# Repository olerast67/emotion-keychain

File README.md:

English | [Русский](README.ru.md)

<div align="center">

# Emotion keychain

**A backpack keychain with a small white OLED screen and a character living on it.**<br>
It blinks, looks around, laughs, gets angry, falls asleep in the dark and reacts to taps, shaking, sound and light.

[Owner's guide](docs/user-guide.en.md) · [Engine](docs/engine.en.md) · [Emotions](docs/emotions.en.md) · [Voice](docs/sound.en.md) · [Encounters](docs/encounters.en.md) · [Hardware](docs/hardware.en.md) · [Board](hardware/rev-b/README.en.md) · [Case](hardware/rev-b/case/README.en.md) · [Power](docs/power.en.md) · [Plan](docs/plan.en.md)

</div>

---

> [!IMPORTANT]
> **Project status**
> - **Works today:** the face engine, the simulators (desktop and browser) and the **ESP32 test stand** — a cheap dev board with a real OLED screen.
> - **Designed, not built yet:** the **rev B keychain board**. It passes DRC and a full simulation of its firmware, but it has **not been fabricated or tested** on real hardware. Order it only if you are fine with being the first to try it.
> - **Battery life numbers are estimates** from a simulation of the board, not measurements.

## Three ways in

| | | |
|---|---|---|
| **Try it in the browser** | No hardware, nothing to install. Tap the face, shake it, turn off the lights, start a duel with a neighbour. | [olerast67.github.io/emotion-keychain](https://olerast67.github.io/emotion-keychain/) |
| **Build the ~$10 ESP32 version** | Any ESP32 dev board (C5, classic, C3 or S3), a 0.96″ SSD1306 module and four wires. Optional touch button and piezo. Flash it from the browser on [olerast.com](https://olerast.com/projects/emotion-keychain/flash). | [ESP32 stand](firmware/README.en.md#esp32-stand) |
| **Make the rev B keychain** | The real thing: a 30 × 46 mm nRF52840 board in an acrylic case, with sensors, a piezo voice, vibration and a Li-Po cell. Not yet tested — see the status above. | [Board](hardware/rev-b/README.en.md) · [Case](hardware/rev-b/case/README.en.md) · [Firmware](firmware/README.en.md#rev-b-board) |

## Features

- **139 emotions.** Joy, laughter, sadness, anger, surprise, sleep, dizziness, "listening", "eating" while charging — and memes: the screaming soyjak, Lenny, `¯\_(ツ)_/¯`, FFFUUU, `$_$`, the table flip. [Full catalogue](docs/emotions.en.md).
- **Every face is alive.** Blinking, gaze, moving pupils and a signature gesture each: breathing, eyebrows, squinting, head tilt, chatter. Transitions are smooth, and eye shape changes hide behind a blink.
- **Ten characters:** playful, grumpy, sleepy, shy, curious, chill, drama, glitchy, sly and kind. Each has its own resting face, its own answer to touches, its own hobbies, tempo and voice. The character and looks come from the chip's serial number, so no two keychains are the same. One in a hundred is legendary, with a golden cyber eye.
- **It reacts to the world.** Taps, shaking, falls, claps, music, darkness, cold, charging, long loneliness. Reactions rotate, and annoyance has a ladder from "-_-" to flipping the table.
- **Growth and achievements.** It starts with 44 emotions and unlocks the rest as "implants" for days together, touches, steps and encounters — about a month in all. On top: a streak of days together and 24 achievements with a trophy, from FIRST FRIEND to MARATHON and 1337.
- **Synthesized voice.** A piezo buzzer answers touches with short "words" made of notes, R2-D2 style, and every character has its own pitch and manner. Scenes have their own music, from a modem handshake during a "hack" to Happy Birthday. [How it sounds](docs/sound.en.md).
- **Encounters and duels over Bluetooth, without pairing.** Two keychains nearby find each other on their own, become friends day by day from NEW FRIEND to BFF, duel, and the older one gifts the younger an emotion. After a duel they chat in a beeping cipher. [Protocol](docs/encounters.en.md).
- **Surprises and easter eggs.** Fake hacks, hiding, reboots, ERROR 404: MOOD NOT FOUND, a ":(" blue screen, holidays and your birthday, H4X0R MODE at 13:37, and a logo bouncing until it hits the corner while charging.
- **Three themes:** classic, cyberpunk and retro (big pixels like an old handheld).
- **Kind to the battery.** A frame is drawn only when the face changes, only the changed parts go to the screen, and the CPU sleeps between frames.
- **One codebase everywhere:** the rev B firmware (nRF52840), the ESP32 stand, desktop simulators and the browser page.

<div align="center">

</div>

## How it works

```mermaid
flowchart LR
  IMU["Accelerometer<br/>tap · shake · fall · steps"] --> B
  MIC["Microphone<br/>speech · music · clap"] --> B
  LUX["Light sensor<br/>dark · bright"] --> B
  PWR["Battery and USB<br/>charge · charging"] --> B
  CLK["Clock<br/>day · night"] --> B
  B["Behavior<br/>mood and reactions"] --> E["FaceEngine<br/>face · transitions · gestures"]
  E -- "changed windows only" --> D["SSD1306<br/>128×64 over I2C"]
  B --> V["Voice<br/>phrases · scene music"]
  V -- "PWM frequency" --> Z["Piezo"]
```

Details are in the [engine description](docs/engine.en.md).

## The rev B keychain

<div align="center">

</div>

<table>
<tr>
<td width="50%"></td>
<td width="50%"></td>
</tr>
<tr>
<td align="center">Assembled: the screen behind a clear cover</td>
<td align="center">Exploded: acrylic layers, screen module and board</td>
</tr>
</table>

| | |
|---|---|
| **Screen** | white 0.96″ OLED, SSD1306, 128×64 |
| **Brain** | nRF52840: Raytac MDBT50Q module on the rev B board |
| **Sensors** | LIS3DH accelerometer, PDM microphone, LTR-303ALS light sensor, button |
| **Voice and feedback** | piezo buzzer, vibration motor |
| **Power** | protected Li-Po cell, 402025, 502025 or 602025 (150–250 mAh); USB-C charging at 100 mA, only at 10–42 °C by the nRF die temperature |
| **Board** | 30 × 46 mm plus a ring tab, 4 layers, production files for JLCPCB and PCBWay |
| **Case** | laser-cut acrylic "sandwich", 35 × 51 mm, 18.8 / 19.8 / 20.8 mm thick in three versions S, M, L for different cells |
| **Battery life (estimate)** | a typical day — about 11, 15 and 18 days (S, M, L); 16 h of face a day — about 3–5 days. **Simulation estimate, not measured** |

- **Generated from one description.** Schematic, placement, routing, Gerber, BOM and CPL are built by scripts from [`netlist.py`](hardware/rev-b/gen/netlist.py); nothing is edited by hand in KiCad.
- **Four layers,** a solid ground plane, the antenna at the edge with no copper under it.
- **Assembly:** the factory places the small parts on both sides; by hand you add the screen module, the cell and the vibration motor (about 15 minutes).
- **Ready to order:** production files are in [`hardware/rev-b/out`](hardware/rev-b/out) and [`hardware/rev-b/out/panel`](hardware/rev-b/out/panel). Remember that nobody has built one yet.

Parts, stack-up and sourcing: [docs/hardware.en.md](docs/hardware.en.md). Current budget: [docs/power.en.md](docs/power.en.md). Using the keychain: [owner's guide](docs/user-guide.en.md).

## Repository layout

```
engine/          face engine: C++20, no heap, no exceptions, no libm
  include/face/  headers: face parameters, catalogue, engine, behaviour
  src/           rendering, animation, 139 emotion presets, behaviour
  tests/         tests with no external dependencies
firmware/        firmware: rev B board (nRF52840) and the ESP32 stand
  src/keychain/  rev B: sensors, radio, power, console
  bootloader/    bootloader for the first flash over SWD
  release/       ready-made firmware files
hardware/
  rev-b/         the rev B board: KiCad, Gerber, BOM, CPL, schematic PDF
    gen/         generators: netlist.py, placement, routing, production files
    case/        acrylic case: cut files and a 3D viewer
sim/
  cli/           facegen — GIFs, contact sheets, benchmark, catalogue
  sdl/           facesim — desktop window simulator
  web/           browser simulator (the engine in WebAssembly)
docs/            engine, emotions, hardware, power, plan, owner's guide
tools/           helper scripts
LICENSES/        licence texts (see REUSE.toml)
```

## Build

You need CMake 3.16+ and a C++20 compiler (GCC 10+ or Clang 12+). SDL2 is only needed for the window simulator.

```sh
cmake -S . -B build -DCMAKE_BUILD_TYPE=Release
cmake --build build

./build/face_tests                              # engine tests
./build/facegen list                            # all emotions and clips
./build/facegen anim lenny out/lenny.gif        # one emotion as a GIF
./build/facegen trans neutral laugh out/t.gif   # a transition between two emotions
./build/facegen sheet out/all.gif --scale 2     # contact sheet of all emotions
./build/facegen scene hack out/hack.gif         # a surprise scene (--theme cyber for cyberpunk)
./build/facegen sound all out/voice.wav         # the keychain's voice as WAV (--serial N for another one)
./build/facesim                                 # window with a face (if SDL2 is present)
```

Browser simulator (needs clang with the wasm32 target and wasm-ld from lld):

```sh
sim/web/build.sh    # then open sim/web/dist/index.html, no server needed
```

Firmware (PlatformIO):

```sh
cd firmware
pio run -e esp32c5 -t upload && pio device monitor   # ESP32 stand (also esp32dev, esp32c3, esp32s3)
pio run -e keychain                                  # rev B board → .pio/build/keychain/
```

Ready-made firmware files are in [`firmware/release/`](firmware/release/README.en.md). The first flash of a rev B board goes over SWD with a Raspberry Pi Pico as the programmer, see the [bootloader notes](firmware/bootloader/README.en.md). Board and case generators (KiCad 7, Python) are described in the [board README](hardware/rev-b/README.en.md) and [hardware overview](hardware/README.en.md).

## How this was made

This project was built by a non-expert — not an electronics engineer or a professional programmer — working with an AI assistant, Claude by Anthropic. The engine, the firmware, the board generators, the case and these docs were written in conversation, then checked with tests, simulation, DRC and many review passes. That is also why the status box above is so careful: what has not been tested on real hardware is clearly marked. Bug reports and fixes from people who know better are very welcome.

## Licences

The project is fully open source. You may build, modify and sell keychains, boards and cases under these terms:

| What | Licence | File |
|---|---|---|
| Code: `engine/`, `firmware/`, `sim/`, `tools/`, CMake and scripts | Apache-2.0 | [LICENSE](LICENSE), [NOTICE](NOTICE) |
| Hardware: `hardware/` — KiCad files, generators, Gerber, BOM/CPL, case files | CERN-OHL-W-2.0 | [hardware/LICENSE](hardware/LICENSE), [text](LICENSES/CERN-OHL-W-2.0.txt) |
| Documentation and images: `docs/`, README files, `*.md`, PNG and GIF | CC-BY-4.0 | [text](LICENSES/CC-BY-4.0.txt) |

[REUSE.toml](REUSE.toml) maps every path to its licence. Firmware binaries also contain third-party code under its own licences (the Adafruit nRF52 Arduino core under LGPL-2.1, the Nordic SoftDevice S140 under Nordic's licence, and more): see [THIRD_PARTY_NOTICES.md](THIRD_PARTY_NOTICES.md).

**Trademarks.** The project name, logo, mascot and character art style and the OLERAST brand are not licensed. Forks and derivative products must use a different name; "compatible with Emotion keychain" or "based on Emotion keychain" is fine. See [TRADEMARKS.md](TRADEMARKS.md).

## Contributing

Ideas for new emotions are easiest to file with the [issue template](https://github.com/olerast67/emotion-keychain/issues/new/choose). To add an emotion yourself: add its id to `FACE_EXPR_LIST` in [`engine/include/face/expressions.h`](engine/include/face/expressions.h), describe the preset in [`engine/src/expressions.cpp`](engine/src/expressions.cpp), check it with `./build/facegen anim <id> out/x.gif` and `./build/face_tests`, and regenerate the catalogue with `./build/facegen catalog docs/emotions.md` (CI checks that it matches the code).

## Support

The project is free and open: no ads, no paid features, no accounts. Donations go into test boards, parts and the time it takes to get rev B from "designed" to "tested on real hardware".

&nbsp;

A star on the repository, a photo of the stand you built, or a bug report helps too.

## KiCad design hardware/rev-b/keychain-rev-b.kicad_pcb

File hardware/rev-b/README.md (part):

[English](README.en.md) | Русский

# Плата rev B

> **Статус:** готова к заказу. Перед выпуском плату исправили по полному предрелизному аудиту и независимой проверке: SA0 акселерометра на VDD, ёмкость на выходе REG0 в норме Nordic, перемычки экрана дальше от штырей, заряд по разрешению прошивки, уровень статуса заряда, TVS на VBUS, панель для монтажа, нормы JLCPCB по отверстиям и шёлку ([список](#проверка-перед-заказом)). Переходные 0.25/0.55 мм, переходных в площадках нет. DRC — 0 ошибок, 0 несоединённых, 0 предупреждений (`out/keychain-rev-b-drc.rpt`). Файлы для заказа уже собраны: одна плата — в `out/`, [панель для монтажа](#панель-для-монтажа) — в `out/panel/`. Перед заказом пройдите список [«Что сверить»](#что-сверить-перед-заказом).

Своя плата брелока: модуль nRF52840 (Raytac MDBT50Q), зарядка Li-Po от USB-C, датчики, пищалка, вибро и кнопка. Модуль экрана SSD1306 0.96″ стоит над ней на ушках акриловых рамок корпуса, ячейка — между ними. Как устроена схема и почему так — в [описании железа](../../docs/hardware.md).

Корпус из акрила под лазерную резку и 3D-просмотр собранного брелока — в [`case/`](case/README.md).

Всё генерируется скриптами из одного описания `gen/netlist.py`: схема, плата, трассировка, Gerber, BOM и CPL. Руками в KiCad ничего не правится.

**Для заказа ничего запускать не нужно.** Плата `keychain-rev-b.kicad_pcb` разведена и проверена, файлы для заводов лежат в `out/` и `out/panel/` — их загружают как есть ([JLCPCB](#заказ-на-jlcpcb), [PCBWay](#заказ-на-pcbway)). Скрипты нужны, только чтобы изменить плату:

```sh
cd hardware/rev-b/gen
python3 build.py place --force  # расставить детали заново — плата БЕЗ дорожек (out/work/place-*.png)
python3 build.py route     # переходные земли и питания, шины питания, Freerouting, доводка, заливки, DRC
python3 build.py finish    # доводка разведённой платы без перетрассировки — только проверка, без записи
python3 build.py finish --force  # то же с записью: паста, шёлк и надписи из netlist.py, отверстия
python3 build.py fab       # DRC, Gerber, BOM, CPL, файлы PCBWay, чертежи, превью, панель → out/, out/panel/ (нужен KiKit, ниже)
python3 build.py panel     # DRC платы, потом только панель → out/panel/ (нужен KiKit, ниже)
python3 schematic.py       # схема A3 + сверка с netlist.py → out/keychain-rev-b-schematic.pdf
```

- **`place` и `route` заменяют разведённую плату:** `place` — платой без дорожек, `route` — новой разводкой (Freerouting от прогона к прогону разводит по-разному). Поэтому без `--force` оба отказываются, если в плате уже есть дорожки. После `place --force` нужен `route` — уже без `--force`, дорожек ведь нет.
- **`route` и `finish --force` записывают плату только после чистого DRC.** Не прошла — `keychain-rev-b.kicad_pcb` не тронута, а результат для разбора лежит в `out/work/keychain-rev-b-*-failed.kicad_pcb`, отчёт — в `out/work/keychain-rev-b-drc.rpt`. `route` сначала проверяет Java и Freerouting и только потом трогает плату. `finish` без `--force` ничего не пишет: доводит плату в памяти, гоняет DRC и говорит, изменилась бы плата.
- **`fab` сам прогоняет DRC.** Если есть ошибки, несоединённые площадки, в плате нет дорожек или на площадках деталей, которые завод не ставит, есть паста, он ничего не пишет ни в `out/`, ни в `out/panel/`. Панель он собирает раньше файлов одной платы, в черновик `out/work/panel-new`: не собралась или не прошла проверки — `out/` и `out/panel/` не тронуты; собралась — пишутся файлы одной платы, и черновик целиком заменяет `out/panel/`. `build.py panel` сначала так же проверяет плату и только потом собирает панель.
- **Отчёт `out/keychain-rev-b-drc.rpt` пишет только `fab`** и только для платы, которая прошла. Отчёты `route` и `finish` — в `out/work/`.
- **Если что-то пошло не так**, вернуть плату и файлы из репозитория:

  ```sh
  git checkout -- hardware/rev-b/keychain-rev-b.kicad_pcb hardware/rev-b/Keychain.pretty hardware/rev-b/out
  ```

Нужен именно KiCad 7 (`pcbnew` для Python и `kicad-cli`): на KiCad 8 и новее скрипты не работают. Для превью и чертежей — `cairosvg` (`pip install cairosvg`, путь можно дать в `CAIROSVG`) или `rsvg-convert`, и Pillow. Для `route` — Java 21 и [Freerouting](https://github.com/freerouting/freerouting) 2.1, путь к jar — в `FREEROUTING_JAR`. Для панели — [KiKit](https://github.com/yaqwsx/KiKit) 1.5.1 в Python, где виден `pcbnew` KiCad 7:

```sh
python3 -m venv --system-site-packages ~/kikit-venv && ~/kikit-venv/bin/pip install kikit==1.5.1
KIKIT_PYTHON=~/kikit-venv/bin/python python3 build.py fab     # и так же build.py panel
```

`fab` и `panel` берут KiKit из того `python3`, которым запущены, а если там его нет — из Python по пути в `KIKIT_PYTHON`. Без KiKit `fab` останавливается до того, как что-то записать. `build.py fab --no-panel` собирает файлы одной платы и удаляет `out/panel/`: старая панель уже не совпадала бы с платой.

## Стек и размеры

- **Плата:** 30 × 46 мм и ушко для кольца по центру сверху (полукруг R4.5, отверстие 3.2 мм без металлизации), 4 слоя, 1.6 мм, углы R2.
- **Верхние 18 мм** — модуль nRF антенной к правому краю и датчик света, который смотрит вперёд. Ниже — модуль экрана.
- **Сбоку стек:** стекло и плата модуля экрана → две рамки ячейки из акрила, на их ушках лежит модуль, внутри ячейка Li-Po на тонком двустороннем скотче → эта плата → детали на обороте. Покупных стоек нет.
- **Три версии, S, M и L:** ячейки 402025, 502025 и 602025 (~150, ~200 и ~250 мА·ч), под модулем экрана 6, 7 и 8 мм (рамки ячейки 3 + 3, 3 + 4 и 3 + 5 мм). Плата и прошивка у всех одни и те же, винты корпуса у всех M2 × 25. Ячейка подходит, если:

  > толщина ячейки + 0.3 мм (каптон и скотч под ней) + 0.1 мм (каптон на обороте модуля) + 0.3 мм (вздутие) ≤ высота под модулем − самая высокая деталь на обороте модуля

  Толщину ячейки меряют штангенциркулем в самом толстом месте. Высота под модулем — это две рамки ячейки стопкой, тоже по штангенциркулю: листы акрила гуляют на ±0.1–0.3 мм. Пересчёт по вашим листам — `python3 case.py --sheet 3=… --sheet 4=…` в папке `case/`. Деталь на обороте модуля — 1.1–1.45 мм, смерьте свой модуль. Не влезает — версия на ступень выше. Подробно, вместе с гребёнкой экрана и винтами, — в [README корпуса](case/README.md#три-версии-s-m-l).

| Слой | Что на нём |
|---|---|
| L1 (лицевая) | модуль nRF, датчик света, конденсаторы модуля, площадки ячейки и штырей экрана; длинные сигналы под ячейкой |
| L2 | сплошная земля, без разрезов |
| L3 | шины питания: VBUS, VBAT и VSYS по 0.4 мм, VDD 0.3 мм; медленные сигналы; всё остальное место — земля |
| L4 (оборотная) | остальные детали и сигналы |

Ширины по классам цепей (`NETCLASSES`):

| Класс | Цепи | Дорожка | Где |
|---|---|---|---|
| Power | VBUS, VBAT, VSYS | 0.4 мм | L3 |
| Rail | VDD (3.3 В) | 0.3 мм | L3 |
| Supply | питание экрана и мотора | 0.3 мм | L1, L3, L4 |
| USB | D+, D− | 0.18 мм | L1, L4 |
| Default | сигналы, питание микрофона | 0.15 мм | L1, L3, L4 |

Токи здесь до 0.25 А, 0.4 мм во внутреннем слое держит около 0.7 А. Сигналы в L3 опираются на сплошную землю L2 рядом. Переходные — 0.25/0.55 мм (поясок 0.15 мм): это норма и JLCPCB, и PCBWay.

Порядок трассировки:

1. Каждая площадка земли получает своё переходное в L2, каждая площадка питания — в L3, с зазорами классов цепей.
2. Шины питания в L3 прокладывает свой трассировщик (`gen/powerroute.py`).
3. Сигналы разводит Freerouting; земля для него — плоскость L2, уже проложенное питание закреплено.
4. Что Freerouting не довёл, прокладывает `gen/fixroute.py` по L1, L3 и L4 с переходными, но не в площадках деталей; обрезки и висящие переходные убираются.
5. Заливки земли, сшивка островков, DRC.

Поэтому у питания и земли нет длинных тонких путей по внешним слоям.

## Расстановка по блокам

- **Ушко, лицевая сторона:**
  - модуль;
  - датчик света, его выводы SDA, INT и SCL напротив своих ножек модуля;
  - конденсаторы у ножек питания модуля.
- **Ушко, оборот:**
  - пищалка за модулем, левее антенны;
  - подтяжки шины датчиков;
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
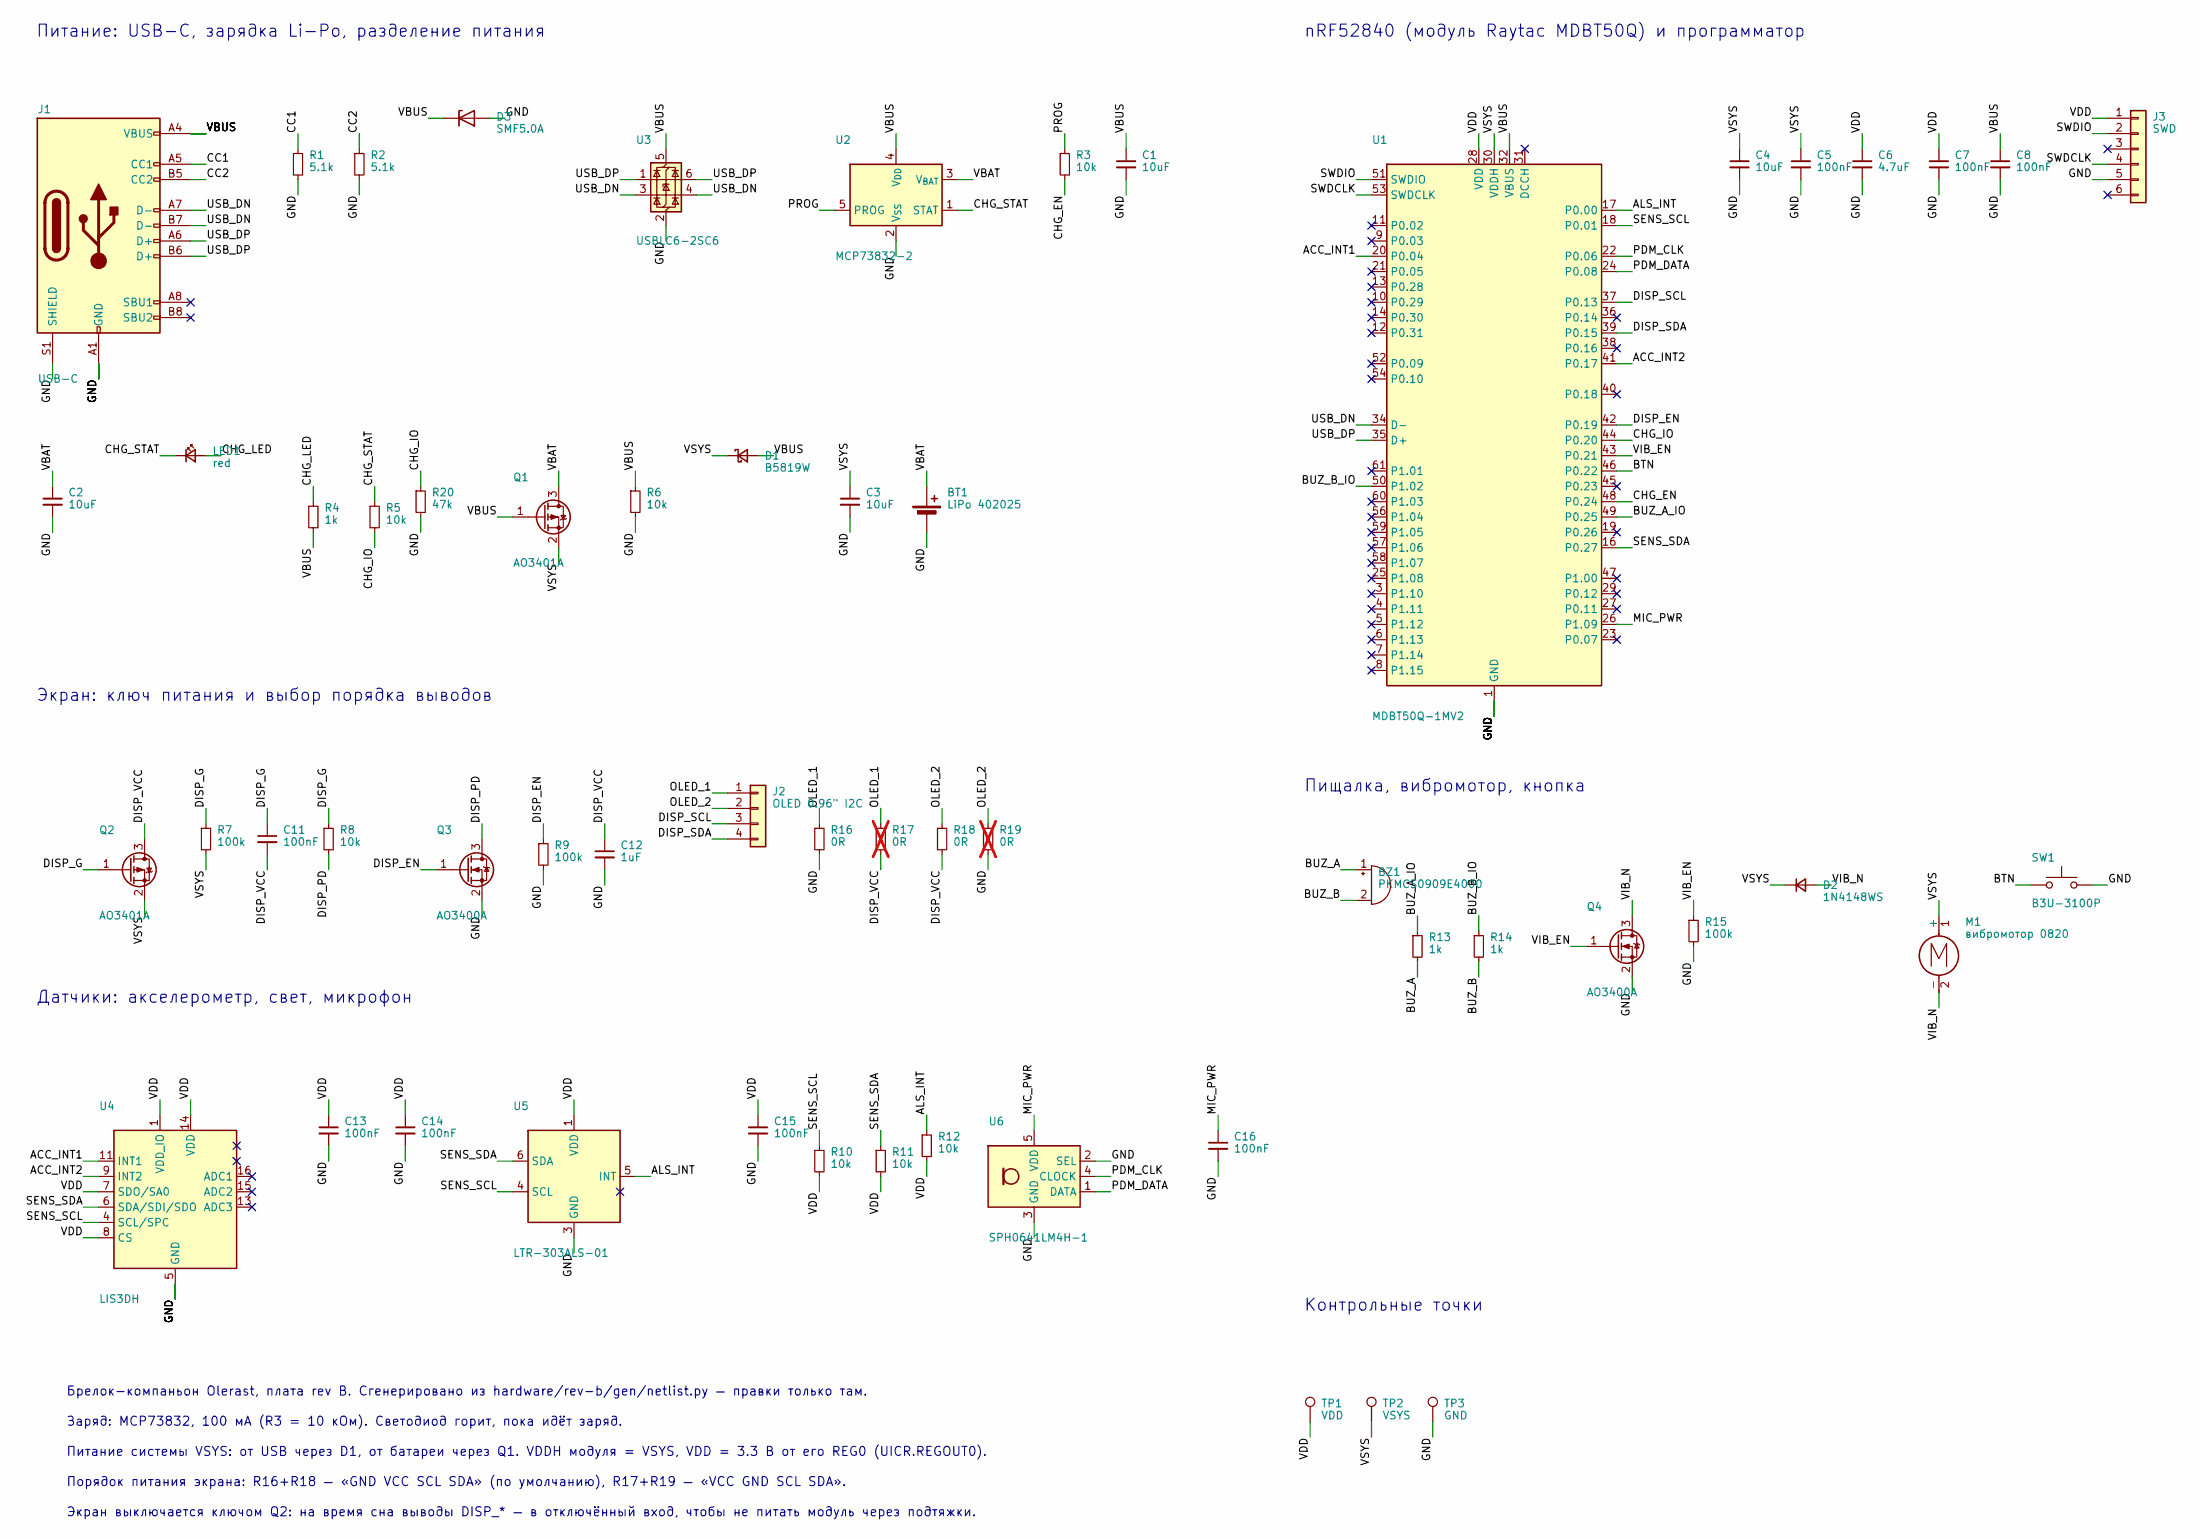
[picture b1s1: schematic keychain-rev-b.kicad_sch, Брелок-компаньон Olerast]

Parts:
BT1: LiPo 402025; LiPo_Pads_20x25mm
BZ1: PKMCS0909E4000; Buzzer_Murata_PKMCS0909E; MPN PKMCS0909E4000-R1; LCSC C910763
C1, C2, C3, C4: 10uF; C_0603_1608Metric; MPN CL10A106KP8NNNC; LCSC C19702
C5, C7, C8, C11, C13, C14, C15, C16: 100nF; C_0402_1005Metric; MPN CL05B104KO5NNNC; LCSC C1525
C6: 4.7uF; C_0603_1608Metric; MPN CL10A475KO8NNNC; LCSC C19666
C12: 1uF; C_0402_1005Metric; MPN CL05A105KA5NQNC; LCSC C52923
D1: B5819W; D_SOD-123; MPN B5819W SL; LCSC C8598
D2: 1N4148WS; D_SOD-323; MPN 1N4148WS; LCSC C2128
D3: SMF5.0A; D_SOD-123F; MPN SMF5.0A; LCSC C1509112
J1: USB-C; USB_C_Receptacle_HRO_TYPE-C-31-M-12; MPN TYPE-C-31-M-12; LCSC C165948
J2: OLED 0.96" I2C; OLED_SSD1306_0.96in_I2C_Module
J3: SWD; Tag-Connect_TC2030-IDC-NL_2x03_P1.27mm_Vertical
LED1: red; LED_0603_1608Metric; MPN KT-0603R; LCSC C2286
M1: вибромотор 0820; VibroMotor_Coin_D8mm
Q1, Q2: AO3401A; SOT-23; MPN AO3401A; LCSC C15127
Q3, Q4: AO3400A; SOT-23; MPN AO3400A; LCSC C20917
R1, R2: 5.1k; R_0402_1005Metric; MPN 0402WGF5101TCE; LCSC C25905
R3, R5, R6, R8, R10, R11, R12: 10k; R_0402_1005Metric; MPN 0402WGF1002TCE; LCSC C25744
R4, R13, R14: 1k; R_0402_1005Metric; MPN 0402WGF1001TCE; LCSC C11702
R7, R9, R15: 100k; R_0402_1005Metric; MPN 0402WGF1003TCE; LCSC C25741
R16, R18: 0R; R_0402_1005Metric; MPN 0402WGF0000TCE; LCSC C17168
R17, R19: 0R; R_0402_1005Metric; MPN 0402WGF0000TCE; LCSC C17168; not fitted
R20: 47k; R_0402_1005Metric; MPN 0402WGF4702TCE; LCSC C25792
SW1: B3U-3100P; SW_SPST_B3U-3100P; MPN B3U-3100P
TP1: VDD; TestPoint_Pad_D1.0mm
TP2: VSYS; TestPoint_Pad_D1.0mm
TP3: GND; TestPoint_Pad_D1.0mm
U1: MDBT50Q-1MV2; Raytac_MDBT50Q; MPN MDBT50Q-1MV2
U2: MCP73832-2; SOT-23-5; MPN MCP73832T-2ACI/OT; LCSC C38066
U3: USBLC6-2SC6; SOT-23-6; MPN USBLC6-2SC6; LCSC C7519
U4: LIS3DH; LGA-16_3x3mm_P0.5mm_LayoutBorder3x5y; MPN LIS3DHTR; LCSC C15134
U5: LTR-303ALS-01; Lite-On_LTR-303ALS-01; MPN LTR-303ALS-01; LCSC C364577
U6: SPH0641LM4H-1; Knowles_LGA-5_3.5x2.65mm; MPN SPH0641LM4H-1; LCSC C497724

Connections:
ACC_INT1: U1.20 (P0.04), U4.11 (INT1)
ACC_INT2: U1.41 (P0.17), U4.9 (INT2)
ALS_INT: R12.1, U1.17 (P0.00), U5.5 (INT)
BTN: SW1.1, U1.46 (P0.22)
BUZ_A: BZ1.1 (+), R13.2
BUZ_A_IO: R13.1, U1.49 (P0.25)
BUZ_B: BZ1.2 (-), R14.2
BUZ_B_IO: R14.1, U1.50 (P1.02)
CC1: J1.A5 (CC1), R1.1
CC2: J1.B5 (CC2), R2.1
CHG_EN: R3.2, U1.48 (P0.24)
CHG_IO: R5.2, R20.1, U1.44 (P0.20)
CHG_LED: LED1.2 (A), R4.1
CHG_STAT: LED1.1 (K), R5.1, U2.1 (STAT)
DISP_EN: Q3.1 (G), R9.1, U1.42 (P0.19)
DISP_G: C11.1, Q2.1 (G), R7.1, R8.1
DISP_PD: Q3.3 (D), R8.2
DISP_SCL: J2.3, U1.37 (P0.13)
DISP_SDA: J2.4, U1.39 (P0.15)
DISP_VCC: C11.2, C12.1, Q2.3 (D), R17.2, R18.2
GND: BT1.2 (-), C1.2, C2.2, C3.2, C4.2, C5.2, C6.2, C7.2, C8.2, C12.2, C13.2, C14.2, C15.2, C16.2, D3.2 (A), J1.A1 (GND), J1.A12 (GND), J1.B1 (GND), J1.B12 (GND), J1.S1 (SHIELD), J3.5, Q3.2 (S), Q4.2 (S), R1.2, R2.2, R6.2, R9.2, R15.2, R16.2, R19.2, R20.2, SW1.2, SW1.3, TP3.1, U1.1 (GND), U1.2 (GND), U1.15 (GND), U1.33 (GND), U1.55 (GND), U2.2 (V_{SS}), U3.2 (GND), U4.5 (GND), U4.10 (GND), U4.12 (GND), U5.3 (GND), U6.2 (SEL), U6.3 (GND)
MIC_PWR: C16.1, U1.26 (P1.09), U6.5 (VDD)
OLED_1: J2.1, R16.1, R17.1
OLED_2: J2.2, R18.1, R19.1
PDM_CLK: U1.22 (P0.06), U6.4 (CLOCK)
PDM_DATA: U1.24 (P0.08), U6.1 (DATA)
PROG: R3.1, U2.5 (PROG)
SENS_SCL: R10.1, U1.18 (P0.01), U4.4 (SCL/SPC), U5.4 (SCL)
SENS_SDA: R11.1, U1.16 (P0.27), U4.6 (SDA/SDI/SDO), U5.6 (SDA)
SWDCLK: J3.4, U1.53 (SWDCLK)
SWDIO: J3.2, U1.51 (SWDIO)
USB_DN: J1.A7 (D-), J1.B7 (D-), U1.34 (D-), U3.3 (I/O2), U3.4 (I/O2)
USB_DP: J1.A6 (D+), J1.B6 (D+), U1.35 (D+), U3.1 (I/O1), U3.6 (I/O1)
VBAT: BT1.1 (+), C2.1, Q1.3 (D), U2.3 (V_{BAT})
VBUS: C1.1, C8.1, D1.2 (A), D3.1 (K), J1.A4 (VBUS), J1.A9 (VBUS), J1.B4 (VBUS), J1.B9 (VBUS), Q1.1 (G), R4.2, R6.1, U1.32 (VBUS), U2.4 (V_{DD}), U3.5 (VBUS)
VDD: C6.1, C7.1, C13.1, C14.1, C15.1, J3.1, R10.2, R11.2, R12.2, TP1.1, U1.28 (VDD), U4.1 (VDD_IO), U4.7 (SDO/SA0), U4.8 (CS), U4.14 (VDD), U5.1 (VDD)
VIB_EN: Q4.1 (G), R15.1, U1.43 (P0.21)
VIB_N: D2.2 (A), M1.2 (-), Q4.3 (D)
VSYS: C3.1, C4.1, C5.1, D1.1 (K), D2.1 (K), M1.1 (+), Q1.2 (S), Q2.2 (S), R7.2, TP2.1, U1.30 (VDDH)

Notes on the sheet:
Питание: USB-C, зарядка Li-Po, разделение питания
nRF52840 (модуль Raytac MDBT50Q) и программатор
Экран: ключ питания и выбор порядка выводов
Пищалка, вибромотор, кнопка
Датчики: акселерометр, свет, микрофон
Контрольные точки
Брелок-компаньон Olerast, плата rev B. Сгенерировано из hardware/rev-b/gen/netlist.py — правки только там.
Заряд: MCP73832, 100 мА (R3 = 10 кОм). Светодиод горит, пока идёт заряд.
Питание системы VSYS: от USB через D1, от батареи через Q1. VDDH модуля = VSYS, VDD = 3.3 В от его REG0 (UICR.REGOUT0).
Порядок питания экрана: R16+R18 — «GND VCC SCL SDA» (по умолчанию), R17+R19 — «VCC GND SCL SDA».
Экран выключается ключом Q2: на время сна выводы DISP_* — в отключённый вход, чтобы не питать модуль через подтяжки.

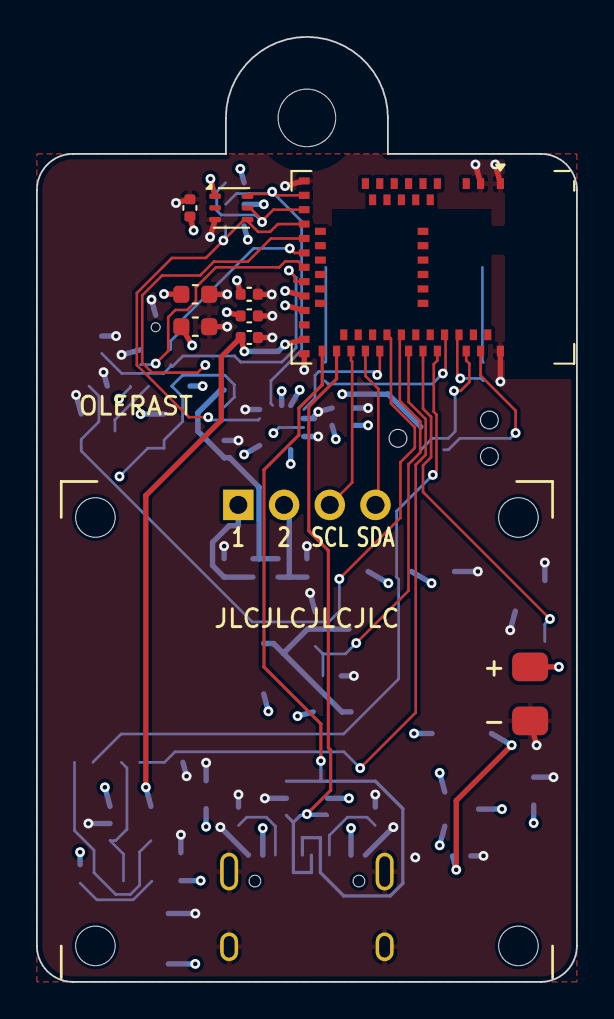
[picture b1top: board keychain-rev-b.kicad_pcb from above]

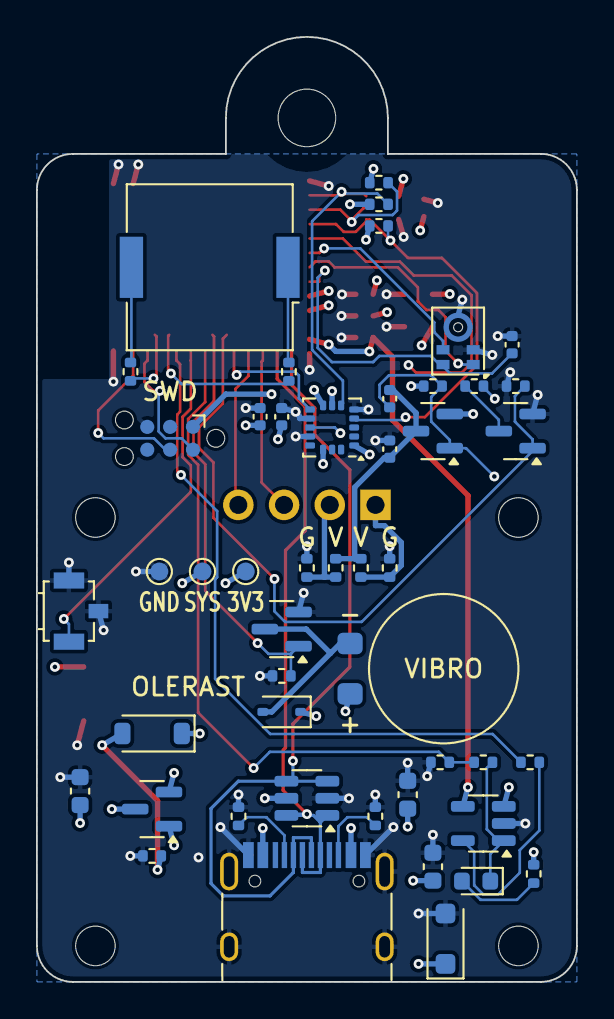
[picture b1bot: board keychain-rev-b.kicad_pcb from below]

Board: 4 copper layers, 30.0 x 52.5 mm, 59 parts (49 on the bottom side), 39 nets.

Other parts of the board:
H1: кольцо брелока или винт корпуса; MountingHole_3.2mm_M3

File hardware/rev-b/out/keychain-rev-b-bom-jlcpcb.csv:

Comment,Designator,Footprint,LCSC,MPN
PKMCS0909E4000,BZ1,Buzzer_Murata_PKMCS0909E,C910763,PKMCS0909E4000-R1
10uF,"C1,C2,C3,C4",C_0603_1608Metric,C19702,CL10A106KP8NNNC
100nF,"C5,C7,C8,C11,C13,C14,C15,C16",C_0402_1005Metric,C1525,CL05B104KO5NNNC
4.7uF,C6,C_0603_1608Metric,C19666,CL10A475KO8NNNC
1uF,C12,C_0402_1005Metric,C52923,CL05A105KA5NQNC
B5819W,D1,D_SOD-123,C8598,B5819W SL
1N4148WS,D2,D_SOD-323,C2128,1N4148WS
SMF5.0A,D3,D_SOD-123F,C1509112,SMF5.0A
USB-C,J1,USB_C_Receptacle_HRO_TYPE-C-31-M-12,C165948,TYPE-C-31-M-12
red,LED1,LED_0603_1608Metric,C2286,KT-0603R
AO3401A,"Q1,Q2",SOT-23,C15127,AO3401A
AO3400A,"Q3,Q4",SOT-23,C20917,AO3400A
5.1k,"R1,R2",R_0402_1005Metric,C25905,0402WGF5101TCE
10k,"R3,R5,R6,R8,R10,R11,R12",R_0402_1005Metric,C25744,0402WGF1002TCE
1k,"R4,R13,R14",R_0402_1005Metric,C11702,0402WGF1001TCE
100k,"R7,R9,R15",R_0402_1005Metric,C25741,0402WGF1003TCE
0R,"R16,R18",R_0402_1005Metric,C17168,0402WGF0000TCE
47k,R20,R_0402_1005Metric,C25792,0402WGF4702TCE
B3U-3100P,SW1,SW_SPST_B3U-3100P,,B3U-3100P
MDBT50Q-1MV2,U1,Raytac_MDBT50Q,,MDBT50Q-1MV2
MCP73832-2,U2,SOT-23-5,C38066,MCP73832T-2ACI/OT
USBLC6-2SC6,U3,SOT-23-6,C7519,USBLC6-2SC6
LIS3DH,U4,LGA-16_3x3mm_P0.5mm_LayoutBorder3x5y,C15134,LIS3DHTR
LTR-303ALS-01,U5,Lite-On_LTR-303ALS-01,C364577,LTR-303ALS-01
SPH0641LM4H-1,U6,Knowles_LGA-5_3.5x2.65mm,C497724,SPH0641LM4H-1

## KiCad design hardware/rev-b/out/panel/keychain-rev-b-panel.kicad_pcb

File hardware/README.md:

[English](README.en.md) | Русский

# Платы

Проекты плат в KiCad. Все файлы платы — схема, разводка, Gerber, BOM и CPL — генерируются скриптами из одного описания (у rev B — `rev-b/gen/netlist.py`); руками в KiCad ничего не правится.

| Плата | Что | Статус |
|---|---|---|
| [`rev-b/`](rev-b/README.md) | Своя плата 30 × 46 мм: модуль nRF52840 (Raytac MDBT50Q), зарядник MCP73832 (заряд включает прошивка), датчики, пищалка, вибро, кнопка, USB-C. Стандартный модуль экрана SSD1306 0.96″ по I2C лежит на ушках акриловых рамок корпуса, покупных стоек нет. Корпус — в [`rev-b/case/`](rev-b/case/README.md) | Готова к заказу |
| A | Плата-носитель для XIAO nRF52840 Sense с экраном на стойках M2 | Ранний план, не делался; папки нет |
| C | Следующая ревизия: исправления по первым платам ([план](../docs/plan.md)) | В плане; папки ещё нет |

Как заказать и собрать — в [README платы rev B](rev-b/README.md). Готовая прошивка для прототипов — в [`firmware/release/`](../firmware/release/README.md); брелоки на продажу прошивают своей сборкой со своими номерами (раздел `[sale]` в `firmware/platformio.ini`). Компоненты, стек и решения — в [docs/hardware.md](../docs/hardware.md).

## Правила для плат

- FR4 1.6 мм, чёрная маска, покрытие ENIG, скруглённые углы.
- Вокруг ушка нет дорожек и открытой меди. Между отверстием и краем платы ≥2.5–3 мм материала.
- У USB-C резисторы 2×5.1 кОм на CC, защита линий от статики и TVS на VBUS.
- Антенна модуля — вне меди, подальше от ячейки и от ушка с кольцом.
- SWD — площадки J3 под кабель Tag-Connect TC2030 на обороте, без разъёма. Они нужны только для первой прошивки, до сборки корпуса; дальше прошивка обновляется по USB.

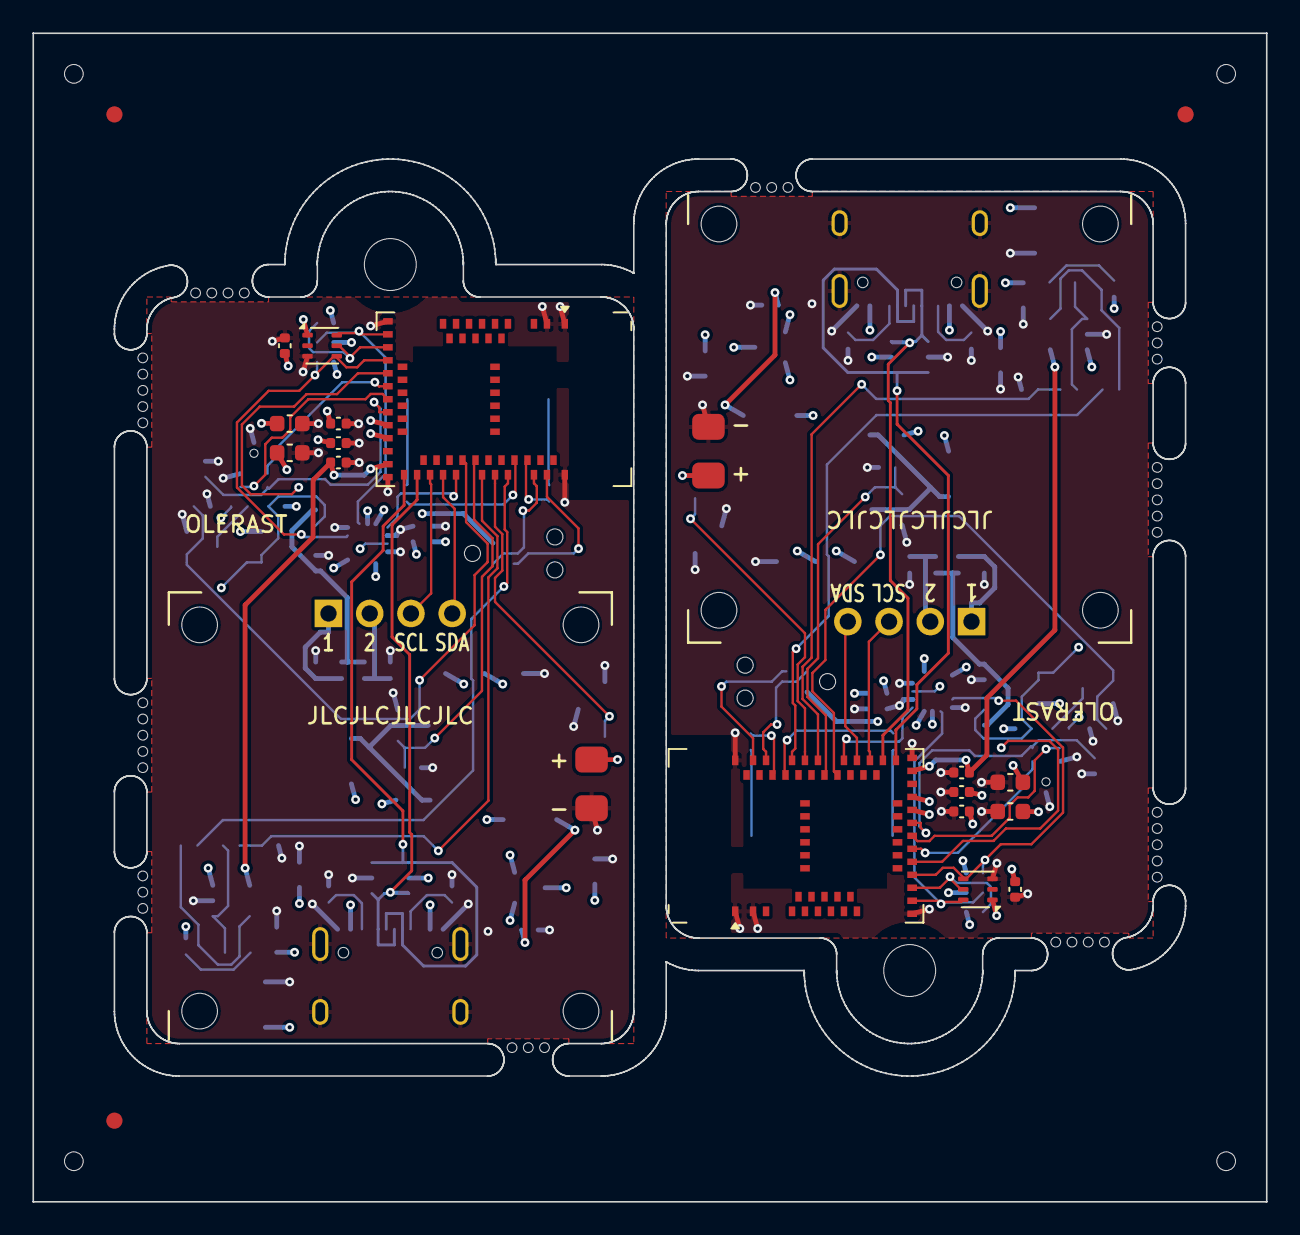
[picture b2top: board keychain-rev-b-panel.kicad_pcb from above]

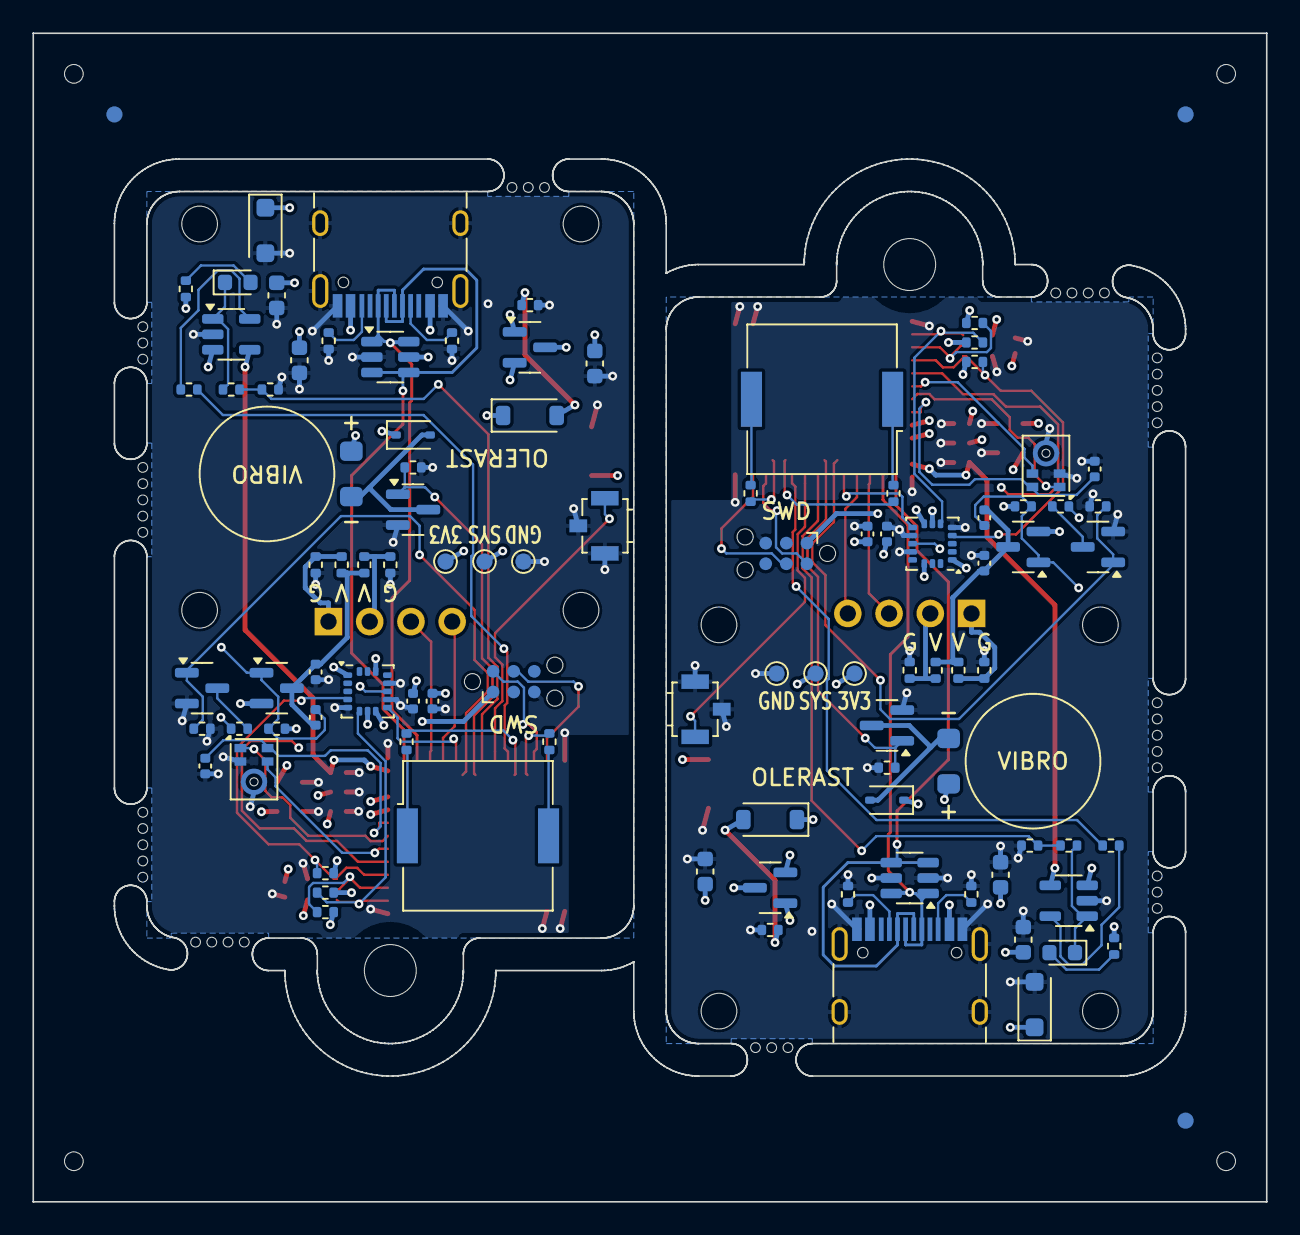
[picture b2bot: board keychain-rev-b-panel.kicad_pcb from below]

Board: 4 copper layers, 76.0 x 72.0 mm, 168 parts (101 on the bottom side), 78 nets.

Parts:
BT1_1, BT1_2: LiPo 402025; LiPo_Pads_20x25mm
BZ1_1, BZ1_2: PKMCS0909E4000; Buzzer_Murata_PKMCS0909E
C1_1, C1_2, C2_1, C2_2, C3_1, C3_2, C4_1, C4_2: 10uF; C_0603_1608Metric
C5_1, C5_2, C7_1, C7_2, C8_1, C8_2, C11_1, C11_2, C13_1, C13_2, C14_1, C14_2, C15_1, C15_2, C16_1, C16_2: 100nF; C_0402_1005Metric
C6_1, C6_2: 4.7uF; C_0603_1608Metric
C12_1, C12_2: 1uF; C_0402_1005Metric
D1_1, D1_2: B5819W; D_SOD-123
D2_1, D2_2: 1N4148WS; D_SOD-323
D3_1, D3_2: SMF5.0A; D_SOD-123F
H1_1, H1_2: кольцо брелока или винт корпуса; MountingHole_3.2mm_M3
J1_1, J1_2: USB-C; USB_C_Receptacle_HRO_TYPE-C-31-M-12
J2_1, J2_2: OLED 0.96" I2C; OLED_SSD1306_0.96in_I2C_Module
J3_1, J3_2: SWD; Tag-Connect_TC2030-IDC-NL_2x03_P1.27mm_Vertical
KiKit_FID_B_1, KiKit_FID_B_2, KiKit_FID_B_3: Fiducial
KiKit_FID_T_1, KiKit_FID_T_2, KiKit_FID_T_3: Fiducial
KiKit_MB_1_2, KiKit_MB_1_3, KiKit_MB_1_4, KiKit_MB_1_5, KiKit_MB_1_6, KiKit_MB_2_2, KiKit_MB_2_3, KiKit_MB_2_4, KiKit_MB_2_5, KiKit_MB_2_6, KiKit_MB_3_2, KiKit_MB_3_3, KiKit_MB_3_4, KiKit_MB_4_2, KiKit_MB_4_3, KiKit_MB_4_4, KiKit_MB_4_5, KiKit_MB_5_2, KiKit_MB_5_3, KiKit_MB_5_4, KiKit_MB_6_2, KiKit_MB_6_3, KiKit_MB_6_4, KiKit_MB_6_5, KiKit_MB_6_6, KiKit_MB_7_2, KiKit_MB_7_3, KiKit_MB_7_4, KiKit_MB_7_5, KiKit_MB_7_6, KiKit_MB_8_2, KiKit_MB_8_3, KiKit_MB_8_4, KiKit_MB_9_2, KiKit_MB_9_3, KiKit_MB_9_4, KiKit_MB_9_5, KiKit_MB_10_2, KiKit_MB_10_3, KiKit_MB_10_4: NPTH
KiKit_TO_1, KiKit_TO_2, KiKit_TO_3, KiKit_TO_4: NPTH
LED1_1, LED1_2: red; LED_0603_1608Metric
M1_1, M1_2: вибромотор 0820; VibroMotor_Coin_D8mm
Q1_1, Q1_2, Q2_1, Q2_2: AO3401A; SOT-23
Q3_1, Q3_2, Q4_1, Q4_2: AO3400A; SOT-23
R1_1, R1_2, R2_1, R2_2: 5.1k; R_0402_1005Metric
R3_1, R3_2, R5_1, R5_2, R6_1, R6_2, R8_1, R8_2, R10_1, R10_2, R11_1, R11_2, R12_1, R12_2: 10k; R_0402_1005Metric
R4_1, R4_2, R13_1, R13_2, R14_1, R14_2: 1k; R_0402_1005Metric
R7_1, R7_2, R9_1, R9_2, R15_1, R15_2: 100k; R_0402_1005Metric
R16_1, R16_2, R17_1, R17_2, R18_1, R18_2, R19_1, R19_2: 0R; R_0402_1005Metric
R20_1, R20_2: 47k; R_0402_1005Metric
SW1_1, SW1_2: B3U-3100P; SW_SPST_B3U-3100P
TP1_1, TP1_2: VDD; TestPoint_Pad_D1.0mm
TP2_1, TP2_2: VSYS; TestPoint_Pad_D1.0mm
TP3_1, TP3_2: GND; TestPoint_Pad_D1.0mm
U1_1, U1_2: MDBT50Q-1MV2; Raytac_MDBT50Q
U2_1, U2_2: MCP73832-2; SOT-23-5
U3_1, U3_2: USBLC6-2SC6; SOT-23-6
U4_1, U4_2: LIS3DH; LGA-16_3x3mm_P0.5mm_LayoutBorder3x5y
U5_1, U5_2: LTR-303ALS-01; Lite-On_LTR-303ALS-01
U6_1, U6_2: SPH0641LM4H-1; Knowles_LGA-5_3.5x2.65mm

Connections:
Board_0-ACC_INT1: U1_1.20, U4_1.11
Board_0-ACC_INT2: U1_1.41, U4_1.9
Board_0-ALS_INT: R12_1.1, U1_1.17, U5_1.5
Board_0-BTN: SW1_1.1, U1_1.46
Board_0-BUZ_A: BZ1_1.1, R13_1.2
Board_0-BUZ_A_IO: R13_1.1, U1_1.49
Board_0-BUZ_B: BZ1_1.2, R14_1.2
Board_0-BUZ_B_IO: R14_1.1, U1_1.50
Board_0-CC1: J1_1.A5, R1_1.1
Board_0-CC2: J1_1.B5, R2_1.1
Board_0-CHG_EN: R3_1.2, U1_1.48
Board_0-CHG_IO: R5_1.2, R20_1.1, U1_1.44
Board_0-CHG_LED: LED1_1.2, R4_1.1
Board_0-CHG_STAT: LED1_1.1, R5_1.1, U2_1.1
Board_0-DISP_EN: Q3_1.1, R9_1.1, U1_1.42
Board_0-DISP_G: C11_1.1, Q2_1.1, R7_1.1, R8_1.1
Board_0-DISP_PD: Q3_1.3, R8_1.2
Board_0-DISP_SCL: J2_1.3, U1_1.37
Board_0-DISP_SDA: J2_1.4, U1_1.39
Board_0-DISP_VCC: C11_1.2, C12_1.1, Q2_1.3, R17_1.2, R18_1.2
Board_0-GND: BT1_1.2, C1_1.2, C2_1.2, C3_1.2, C4_1.2, C5_1.2, C6_1.2, C7_1.2, C8_1.2, C12_1.2, C13_1.2, C14_1.2, C15_1.2, C16_1.2, D3_1.2, J1_1.A1, J1_1.A12, J1_1.B1, J1_1.B12, J1_1.S1, J3_1.5, Q3_1.2, Q4_1.2, R1_1.2, R2_1.2, R6_1.2, R9_1.2, R15_1.2, R16_1.2, R19_1.2, R20_1.2, SW1_1.2, SW1_1.3, TP3_1.1, U1_1.1, U1_1.2, U1_1.15, U1_1.33, U1_1.55, U2_1.2, U3_1.2, U4_1.5, U4_1.10, U4_1.12, U5_1.3, U6_1.2, U6_1.3
Board_0-MIC_PWR: C16_1.1, U1_1.26, U6_1.5
Board_0-OLED_1: J2_1.1, R16_1.1, R17_1.1
Board_0-OLED_2: J2_1.2, R18_1.1, R19_1.1
Board_0-PDM_CLK: U1_1.22, U6_1.4
Board_0-PDM_DATA: U1_1.24, U6_1.1
Board_0-PROG: R3_1.1, U2_1.5
Board_0-SENS_SCL: R10_1.1, U1_1.18, U4_1.4, U5_1.4
Board_0-SENS_SDA: R11_1.1, U1_1.16, U4_1.6, U5_1.6
Board_0-SWDCLK: J3_1.4, U1_1.53
Board_0-SWDIO: J3_1.2, U1_1.51
Board_0-USB_DN: J1_1.A7, J1_1.B7, U1_1.34, U3_1.3, U3_1.4
Board_0-USB_DP: J1_1.A6, J1_1.B6, U1_1.35, U3_1.1, U3_1.6
Board_0-VBAT: BT1_1.1, C2_1.1, Q1_1.3, U2_1.3
Board_0-VBUS: C1_1.1, C8_1.1, D1_1.2, D3_1.1, J1_1.A4, J1_1.A9, J1_1.B4, J1_1.B9, Q1_1.1, R4_1.2, R6_1.1, U1_1.32, U2_1.4, U3_1.5
Board_0-VDD: C6_1.1, C7_1.1, C13_1.1, C14_1.1, C15_1.1, J3_1.1, R10_1.2, R11_1.2, R12_1.2, TP1_1.1, U1_1.28, U4_1.1, U4_1.7, U4_1.8, U4_1.14, U5_1.1
Board_0-VIB_EN: Q4_1.1, R15_1.1, U1_1.43
Board_0-VIB_N: D2_1.2, M1_1.2, Q4_1.3
Board_0-VSYS: C3_1.1, C4_1.1, C5_1.1, D1_1.1, D2_1.1, M1_1.1, Q1_1.2, Q2_1.2, R7_1.2, TP2_1.1, U1_1.30
Board_1-ACC_INT1: U1_2.20, U4_2.11
Board_1-ACC_INT2: U1_2.41, U4_2.9
Board_1-ALS_INT: R12_2.1, U1_2.17, U5_2.5
Board_1-BTN: SW1_2.1, U1_2.46
Board_1-BUZ_A: BZ1_2.1, R13_2.2
Board_1-BUZ_A_IO: R13_2.1, U1_2.49
Board_1-BUZ_B: BZ1_2.2, R14_2.2
Board_1-BUZ_B_IO: R14_2.1, U1_2.50
Board_1-CC1: J1_2.A5, R1_2.1
Board_1-CC2: J1_2.B5, R2_2.1
Board_1-CHG_EN: R3_2.2, U1_2.48
Board_1-CHG_IO: R5_2.2, R20_2.1, U1_2.44
Board_1-CHG_LED: LED1_2.2, R4_2.1
Board_1-CHG_STAT: LED1_2.1, R5_2.1, U2_2.1
Board_1-DISP_EN: Q3_2.1, R9_2.1, U1_2.42
Board_1-DISP_G: C11_2.1, Q2_2.1, R7_2.1, R8_2.1
Board_1-DISP_PD: Q3_2.3, R8_2.2
Board_1-DISP_SCL: J2_2.3, U1_2.37
Board_1-DISP_SDA: J2_2.4, U1_2.39
Board_1-DISP_VCC: C11_2.2, C12_2.1, Q2_2.3, R17_2.2, R18_2.2
Board_1-GND: BT1_2.2, C1_2.2, C2_2.2, C3_2.2, C4_2.2, C5_2.2, C6_2.2, C7_2.2, C8_2.2, C12_2.2, C13_2.2, C14_2.2, C15_2.2, C16_2.2, D3_2.2, J1_2.A1, J1_2.A12, J1_2.B1, J1_2.B12, J1_2.S1, J3_2.5, Q3_2.2, Q4_2.2, R1_2.2, R2_2.2, R6_2.2, R9_2.2, R15_2.2, R16_2.2, R19_2.2, R20_2.2, SW1_2.2, SW1_2.3, TP3_2.1, U1_2.1, U1_2.2, U1_2.15, U1_2.33, U1_2.55, U2_2.2, U3_2.2, U4_2.5, U4_2.10, U4_2.12, U5_2.3, U6_2.2, U6_2.3
Board_1-MIC_PWR: C16_2.1, U1_2.26, U6_2.5
Board_1-OLED_1: J2_2.1, R16_2.1, R17_2.1
Board_1-OLED_2: J2_2.2, R18_2.1, R19_2.1
Board_1-PDM_CLK: U1_2.22, U6_2.4
Board_1-PDM_DATA: U1_2.24, U6_2.1
Board_1-PROG: R3_2.1, U2_2.5
Board_1-SENS_SCL: R10_2.1, U1_2.18, U4_2.4, U5_2.4
Board_1-SENS_SDA: R11_2.1, U1_2.16, U4_2.6, U5_2.6
Board_1-SWDCLK: J3_2.4, U1_2.53
Board_1-SWDIO: J3_2.2, U1_2.51
Board_1-USB_DN: J1_2.A7, J1_2.B7, U1_2.34, U3_2.3, U3_2.4
Board_1-USB_DP: J1_2.A6, J1_2.B6, U1_2.35, U3_2.1, U3_2.6
Board_1-VBAT: BT1_2.1, C2_2.1, Q1_2.3, U2_2.3
Board_1-VBUS: C1_2.1, C8_2.1, D1_2.2, D3_2.1, J1_2.A4, J1_2.A9, J1_2.B4, J1_2.B9, Q1_2.1, R4_2.2, R6_2.1, U1_2.32, U2_2.4, U3_2.5
Board_1-VDD: C6_2.1, C7_2.1, C13_2.1, C14_2.1, C15_2.1, J3_2.1, R10_2.2, R11_2.2, R12_2.2, TP1_2.1, U1_2.28, U4_2.1, U4_2.7, U4_2.8, U4_2.14, U5_2.1
Board_1-VIB_EN: Q4_2.1, R15_2.1, U1_2.43
Board_1-VIB_N: D2_2.2, M1_2.2, Q4_2.3
Board_1-VSYS: C3_2.1, C4_2.1, C5_2.1, D1_2.1, D2_2.1, M1_2.1, Q1_2.2, Q2_2.2, R7_2.2, TP2_2.1, U1_2.30

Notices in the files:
README.md:
Hardware: CERN-OHL-W-2.0
Docs: CC-BY-4.0
